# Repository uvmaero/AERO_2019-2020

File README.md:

# AERO_2019-2020

For all boards / designs specific to 2019 - 2020, CleanSpeed4.5

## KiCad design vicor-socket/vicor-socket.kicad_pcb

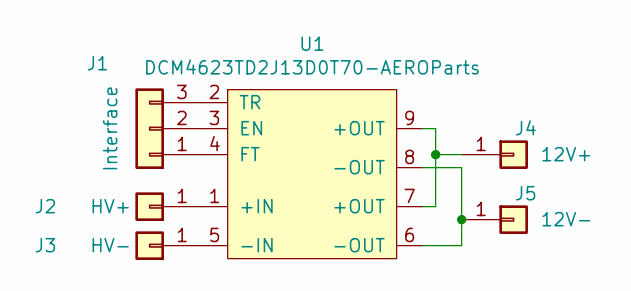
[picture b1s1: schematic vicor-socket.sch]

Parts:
J1: Interface; PinHeader_1x03_P2.54mm_Vertical
J2: HV+; MountingHole_3.2mm_M3_Pad_Via
J3: HV-; MountingHole_3.2mm_M3_Pad_Via
J4: 12V+; MountingHole_3.2mm_M3_Pad_Via
J5: 12V-; MountingHole_3.2mm_M3_Pad_Via
U1: DCM4623TD2J13D0T70-AEROParts; DCM4623TD2J13D0T70_w_landpattern

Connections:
unnamed: J1.1, U1.4 (FT)
unnamed: J1.2, U1.3 (EN)
unnamed: J1.3, U1.2 (TR)
unnamed: J2.1, U1.1 (+IN)
unnamed: J3.1, U1.5 (-IN)
unnamed: J4.1, U1.7 (+OUT), U1.9 (+OUT)
unnamed: J5.1, U1.6 (-OUT), U1.8 (-OUT)

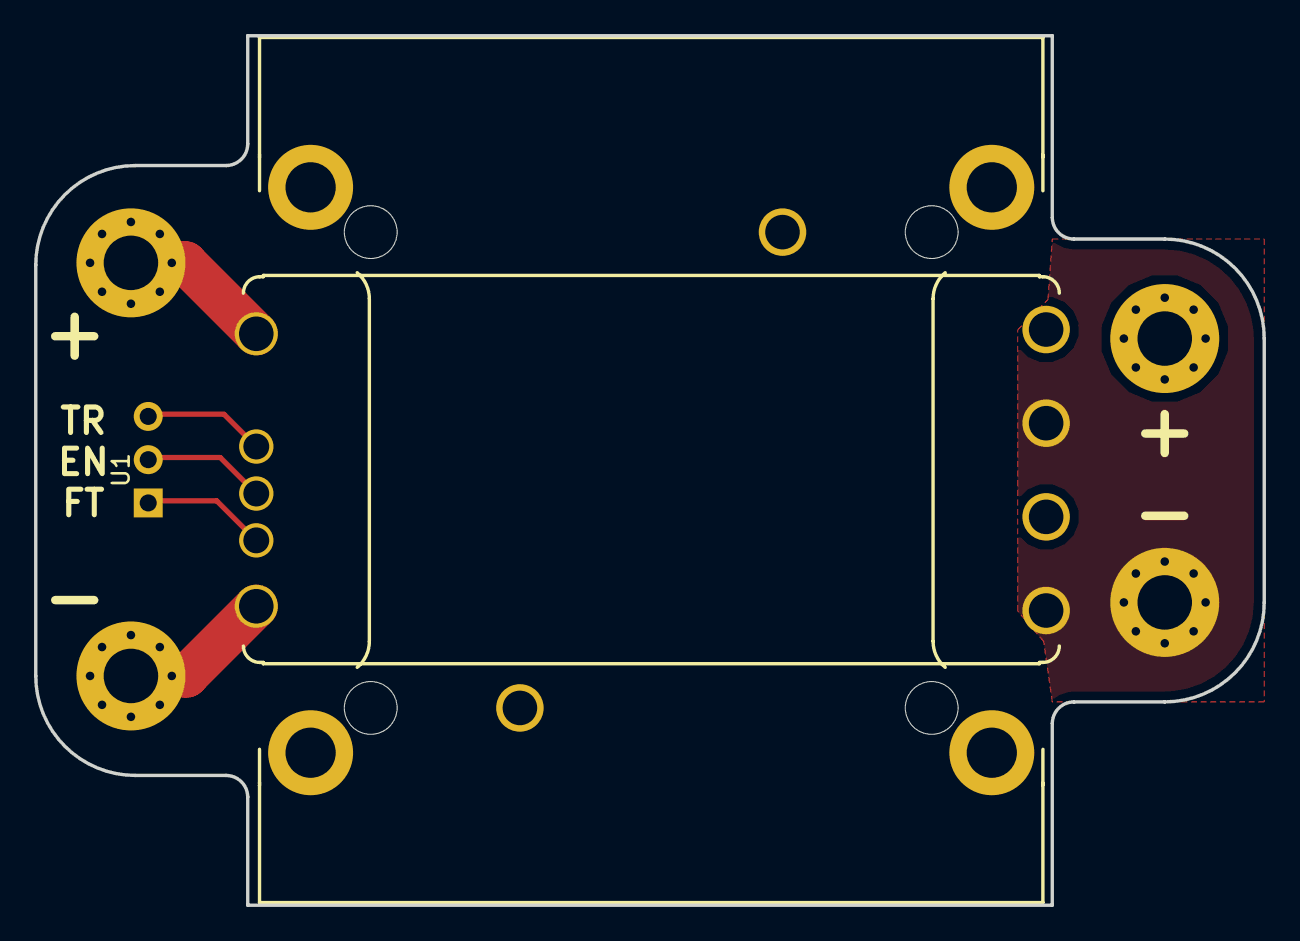
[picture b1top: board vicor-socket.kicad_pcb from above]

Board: 2 copper layers, 72.1 x 51.1 mm, 6 parts (1 on the bottom side), 7 nets.

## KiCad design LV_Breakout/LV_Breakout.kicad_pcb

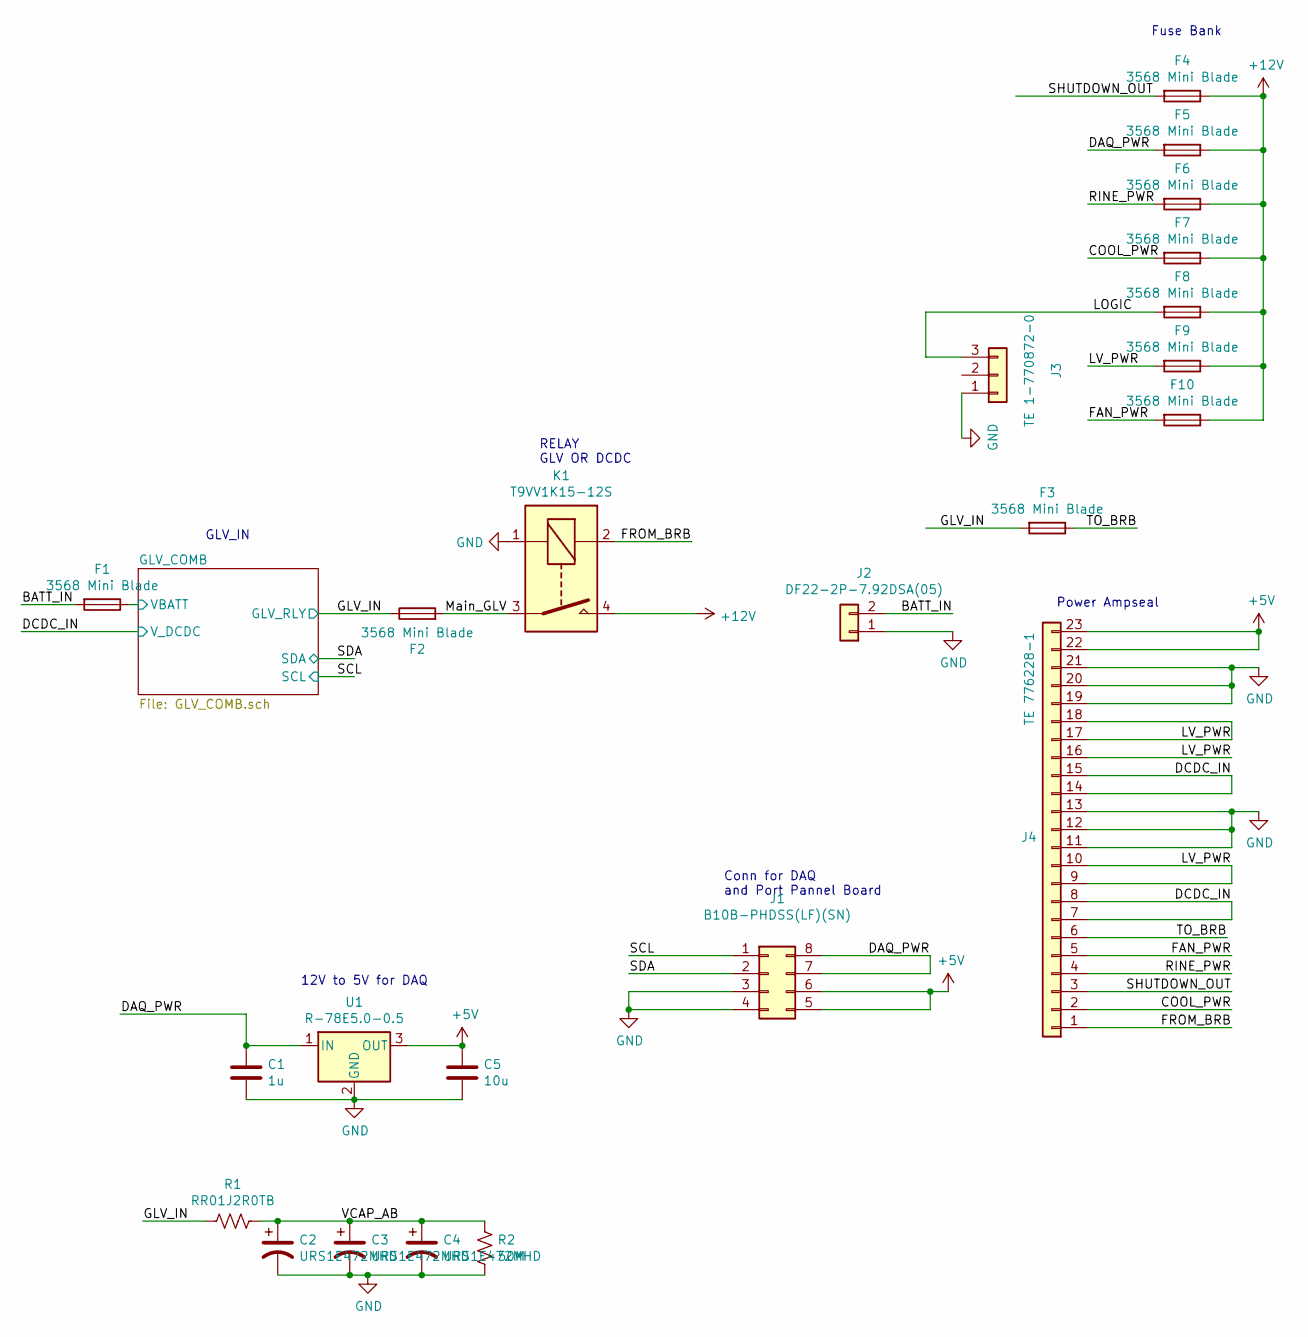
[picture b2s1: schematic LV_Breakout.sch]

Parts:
C1: 1u; C_0603_1608Metric_Pad1.05x0.95mm_HandSolder
C2, C3, C4: URS1E472MHD; CP_Radial_D18.0mm_P7.50mm
C5: 10u; C_0603_1608Metric_Pad1.05x0.95mm_HandSolder
F1, F2, F3, F4, F5, F6, F7, F8, F9, F10: 3568 Mini Blade; Fuseholder_Blade_Mini_Keystone_3568
J1: B10B-PHDSS(LF)(SN); JST_PHD_B8B-PHDSS_2x04_P2.00mm_Vertical
J2: DF22-2P-7.92DSA(05); DF22-2P-7.92DSA05
J3: TE 1-770872-0; TE_MATE-N-LOK_1-770870-x_1x03_P4.14mm_Vertical
J4: TE 776228-1; TE_1-776200-1_23pin_Vertical
K1: T9VV1K15-12S; RELAY_T9VV1K15-12S
R1: RR01J2R0TB; R_Axial_DIN0207_L6.3mm_D2.5mm_P10.16mm_Horizontal
R2: 50M; R_2512_6332Metric_Pad1.52x3.35mm_HandSolder
U1: R-78E5.0-0.5; Converter_DCDC_RECOM_R-78E-0.5_THT

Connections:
+5V: C5.1, J1.5, J1.6, J4.22, J4.23, U1.3 (OUT); also elsewhere on the board
+12V: F4.1, F5.1, F6.1, F7.1, F8.1, F9.1, F10.1, K1.4
/BATT_IN: F1.2, J2.2
/COOL_PWR: F7.2, J4.2
/DAQ_PWR: C1.1, F5.2, J1.7, J1.8, U1.1 (IN)
/DCDC_IN: J4.7, J4.8, J4.14, J4.15; also elsewhere on the board
/FAN_PWR: F10.2, J4.5
/FROM_BRB: J4.1, K1.2
/GLV_COMB/VBATT: F1.1; also elsewhere on the board
/GLV_IN: F2.1, F3.2, R1.2; also elsewhere on the board
/LOGIC: F8.2, J3.3
/LV_PWR: F9.2, J4.9, J4.10, J4.16, J4.17, J4.18
/Main_GLV: F2.2, K1.3
/RINE_PWR: F6.2, J4.4
/SCL: J1.1; also elsewhere on the board
/SDA: J1.2; also elsewhere on the board
/SHUTDOWN_OUT: F4.2, J4.3
/TO_BRB: F3.1, J4.6
/VCAP_AB: C2.1, C3.1, C4.1, R1.1, R2.1
GND: C1.2, C2.2, C3.2, C4.2, C5.2, J1.3, J1.4, J2.1, J3.1, J4.11, J4.12, J4.13, J4.19, J4.20, J4.21, K1.1, R2.2, U1.2 (GND); also elsewhere on the board

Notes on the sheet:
GLV_IN
Power Ampseal
RELAY GLV OR DCDC
Fuse Bank
12V to 5V for DAQ
Conn for DAQ and Port Pannel Board

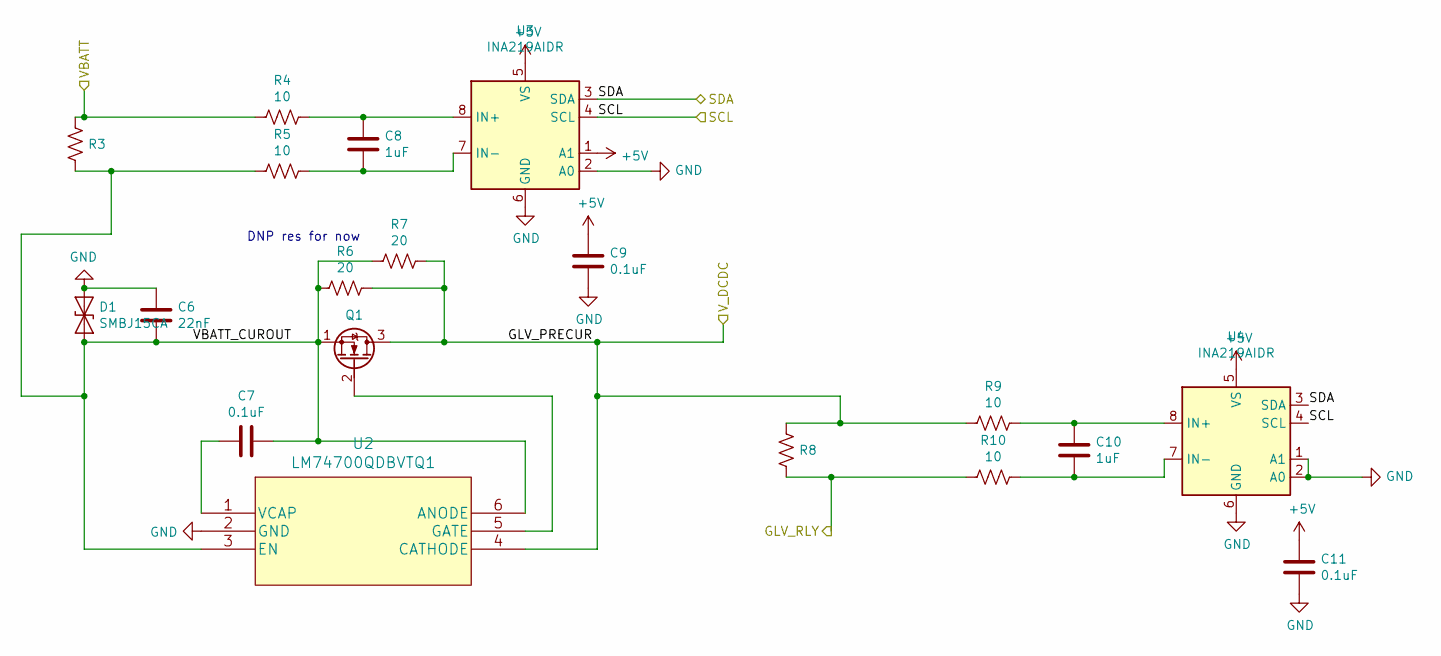
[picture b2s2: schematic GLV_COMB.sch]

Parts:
C6: 22nF; C_0603_1608Metric_Pad1.05x0.95mm_HandSolder
C7, C9, C11: 0.1uF; C_0603_1608Metric_Pad1.05x0.95mm_HandSolder
C8, C10: 1uF; C_0603_1608Metric_Pad1.05x0.95mm_HandSolder
D1: SMBJ15CA; DO-214AA
Q1: CSD18563Q5A; VSONP-8-1EP_5x6_P1.27mm
R3, R8: KRL6432E-M-R003-F-T1
R4, R5, R9, R10: 10; R_0805_2012Metric_Pad1.15x1.40mm_HandSolder
R6, R7: 20; R_2512_6332Metric_Pad1.52x3.35mm_HandSolder
U2: LM74700QDBVTQ1; SOT-23-6_Handsoldering
U3, U4: INA219AIDR; SOIC-8_3.9x4.9mm_P1.27mm

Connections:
+5V: C9.1, C11.1, U3.1 (A1), U3.5 (VS), U4.5 (VS); also elsewhere on the board
/DCDC_IN: Q1.3 (D), R6.1, R7.1, R8.1, R9.2, U2.4 (CATHODE); also elsewhere on the board
/GLV_COMB/VBATT: R3.1, R4.2; also elsewhere on the board
/GLV_COMB/VBATT_CUROUT: C6.2, C7.2, D1.1 (A1), Q1.1 (S), R3.2, R5.2, R6.2, R7.2, U2.3 (EN), U2.6 (ANODE)
/GLV_IN: R8.2, R10.2; also elsewhere on the board
/SCL: U3.4 (SCL), U4.4 (SCL); also elsewhere on the board
/SDA: U3.3 (SDA), U4.3 (SDA); also elsewhere on the board
GND: C6.1, C9.2, C11.2, D1.2 (A2), U2.2 (GND), U3.2 (A0), U3.6 (GND), U4.1 (A1), U4.2 (A0), U4.6 (GND); also elsewhere on the board
unnamed: C7.1, U2.1 (VCAP)
unnamed: C8.1, R4.1, U3.8 (IN+)
unnamed: C8.2, R5.1, U3.7 (IN-)
unnamed: C10.1, R9.1, U4.8 (IN+)
unnamed: C10.2, R10.1, U4.7 (IN-)
unnamed: Q1.2 (G), U2.5 (GATE)

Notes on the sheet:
DNP res for now

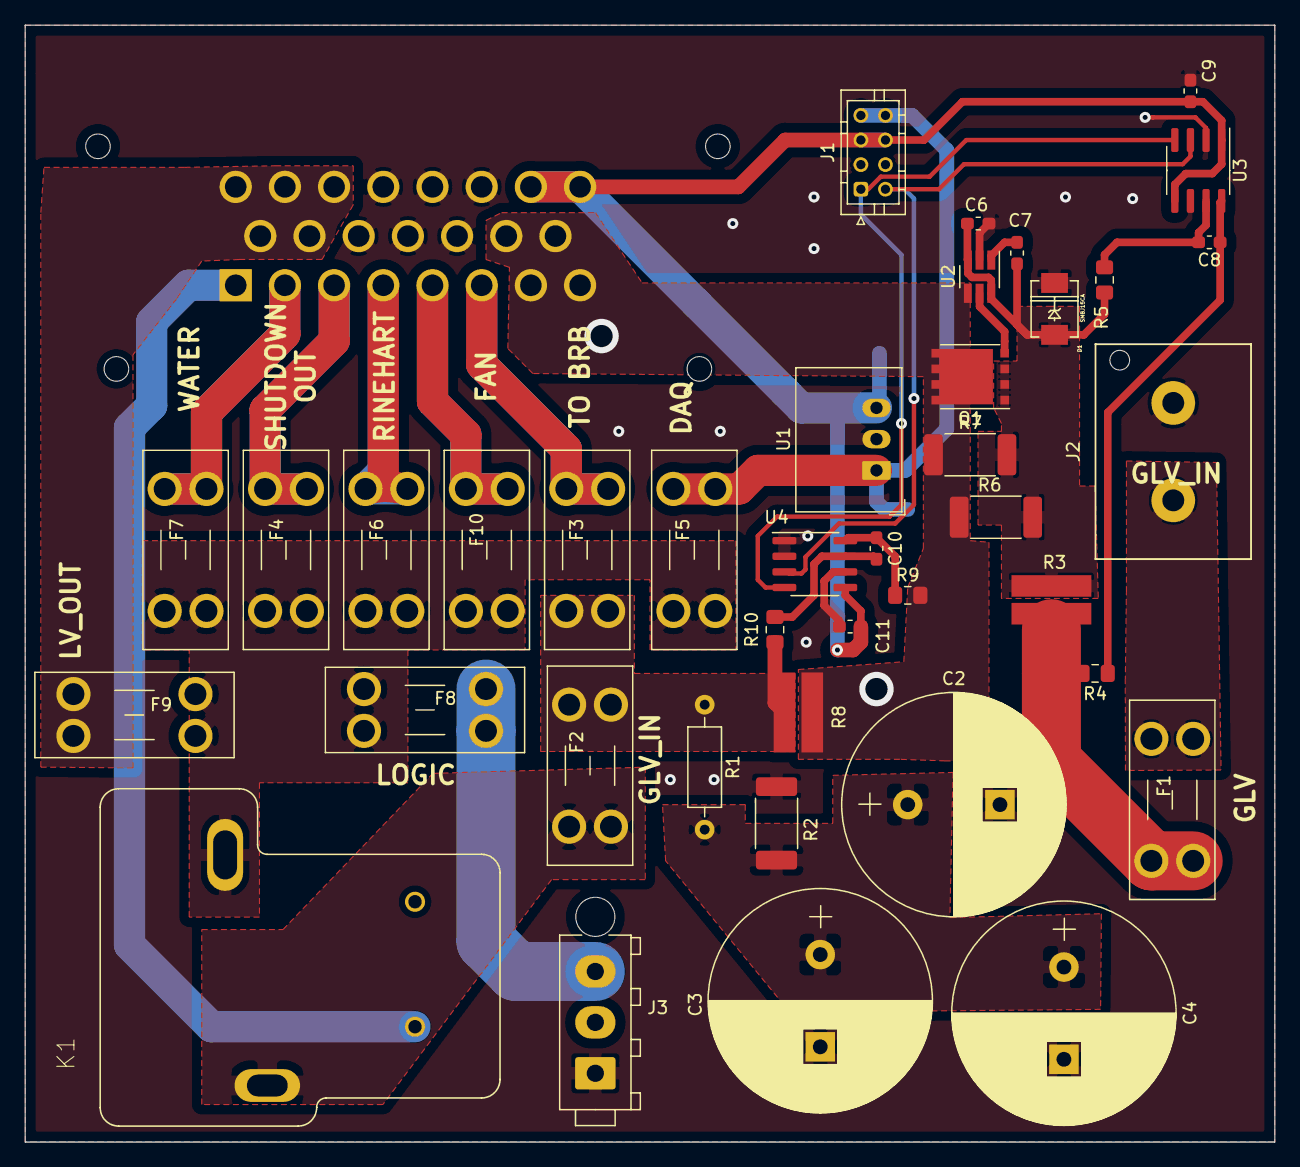
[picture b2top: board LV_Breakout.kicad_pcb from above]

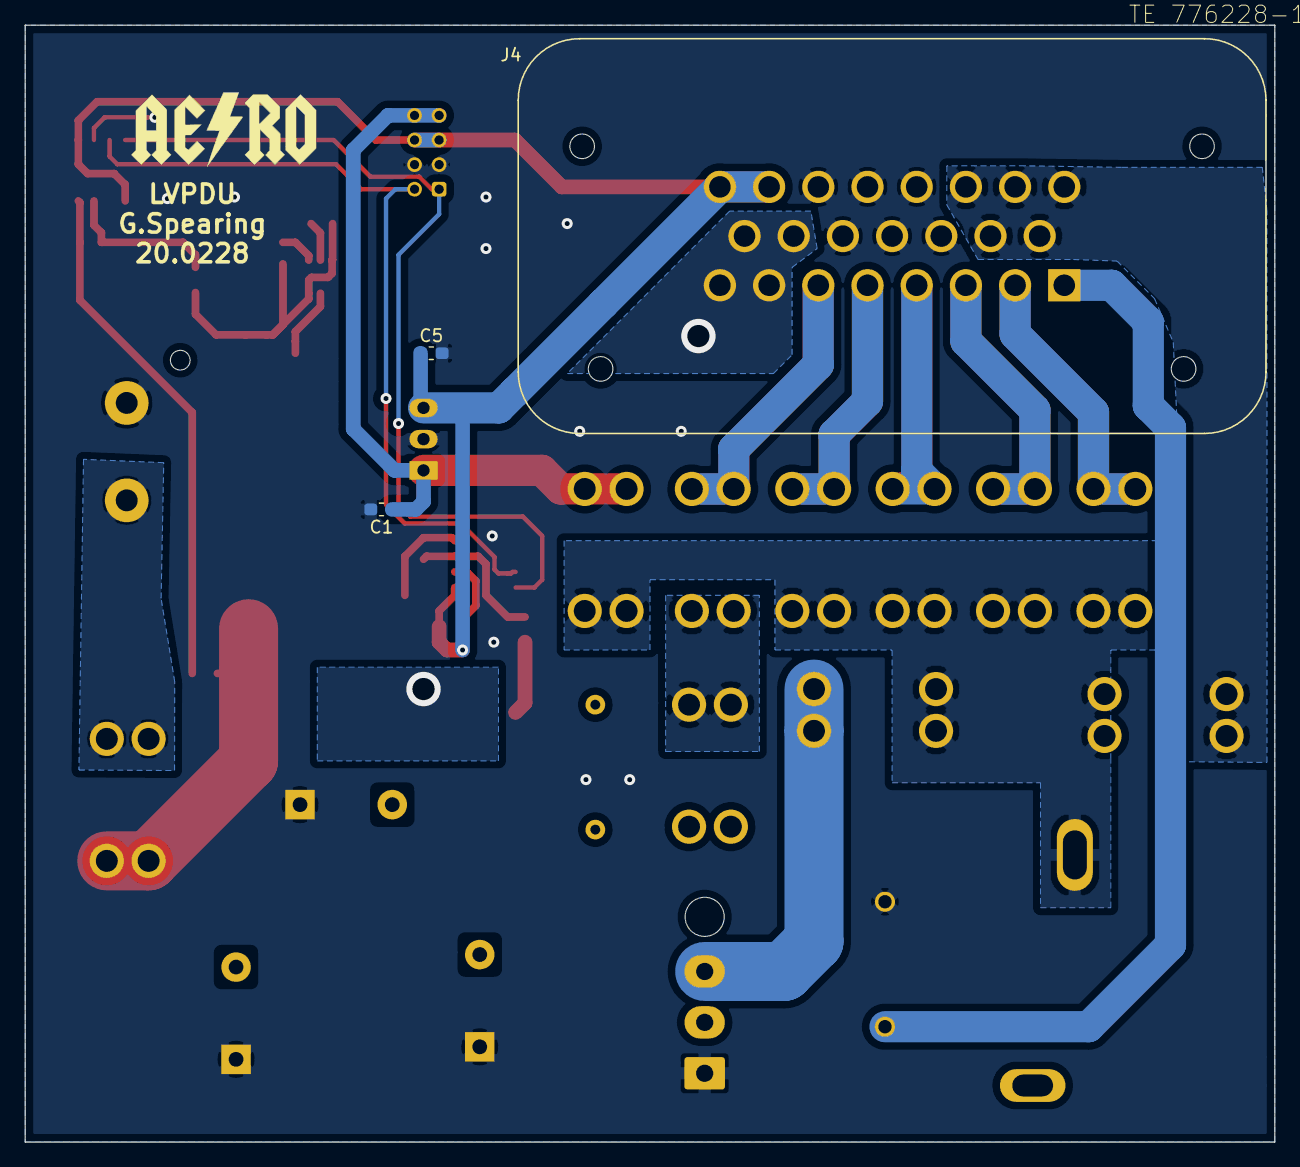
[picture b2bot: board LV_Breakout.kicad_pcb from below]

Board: 2 copper layers, 101.6 x 90.8 mm, 42 parts (3 on the bottom side), 27 nets.

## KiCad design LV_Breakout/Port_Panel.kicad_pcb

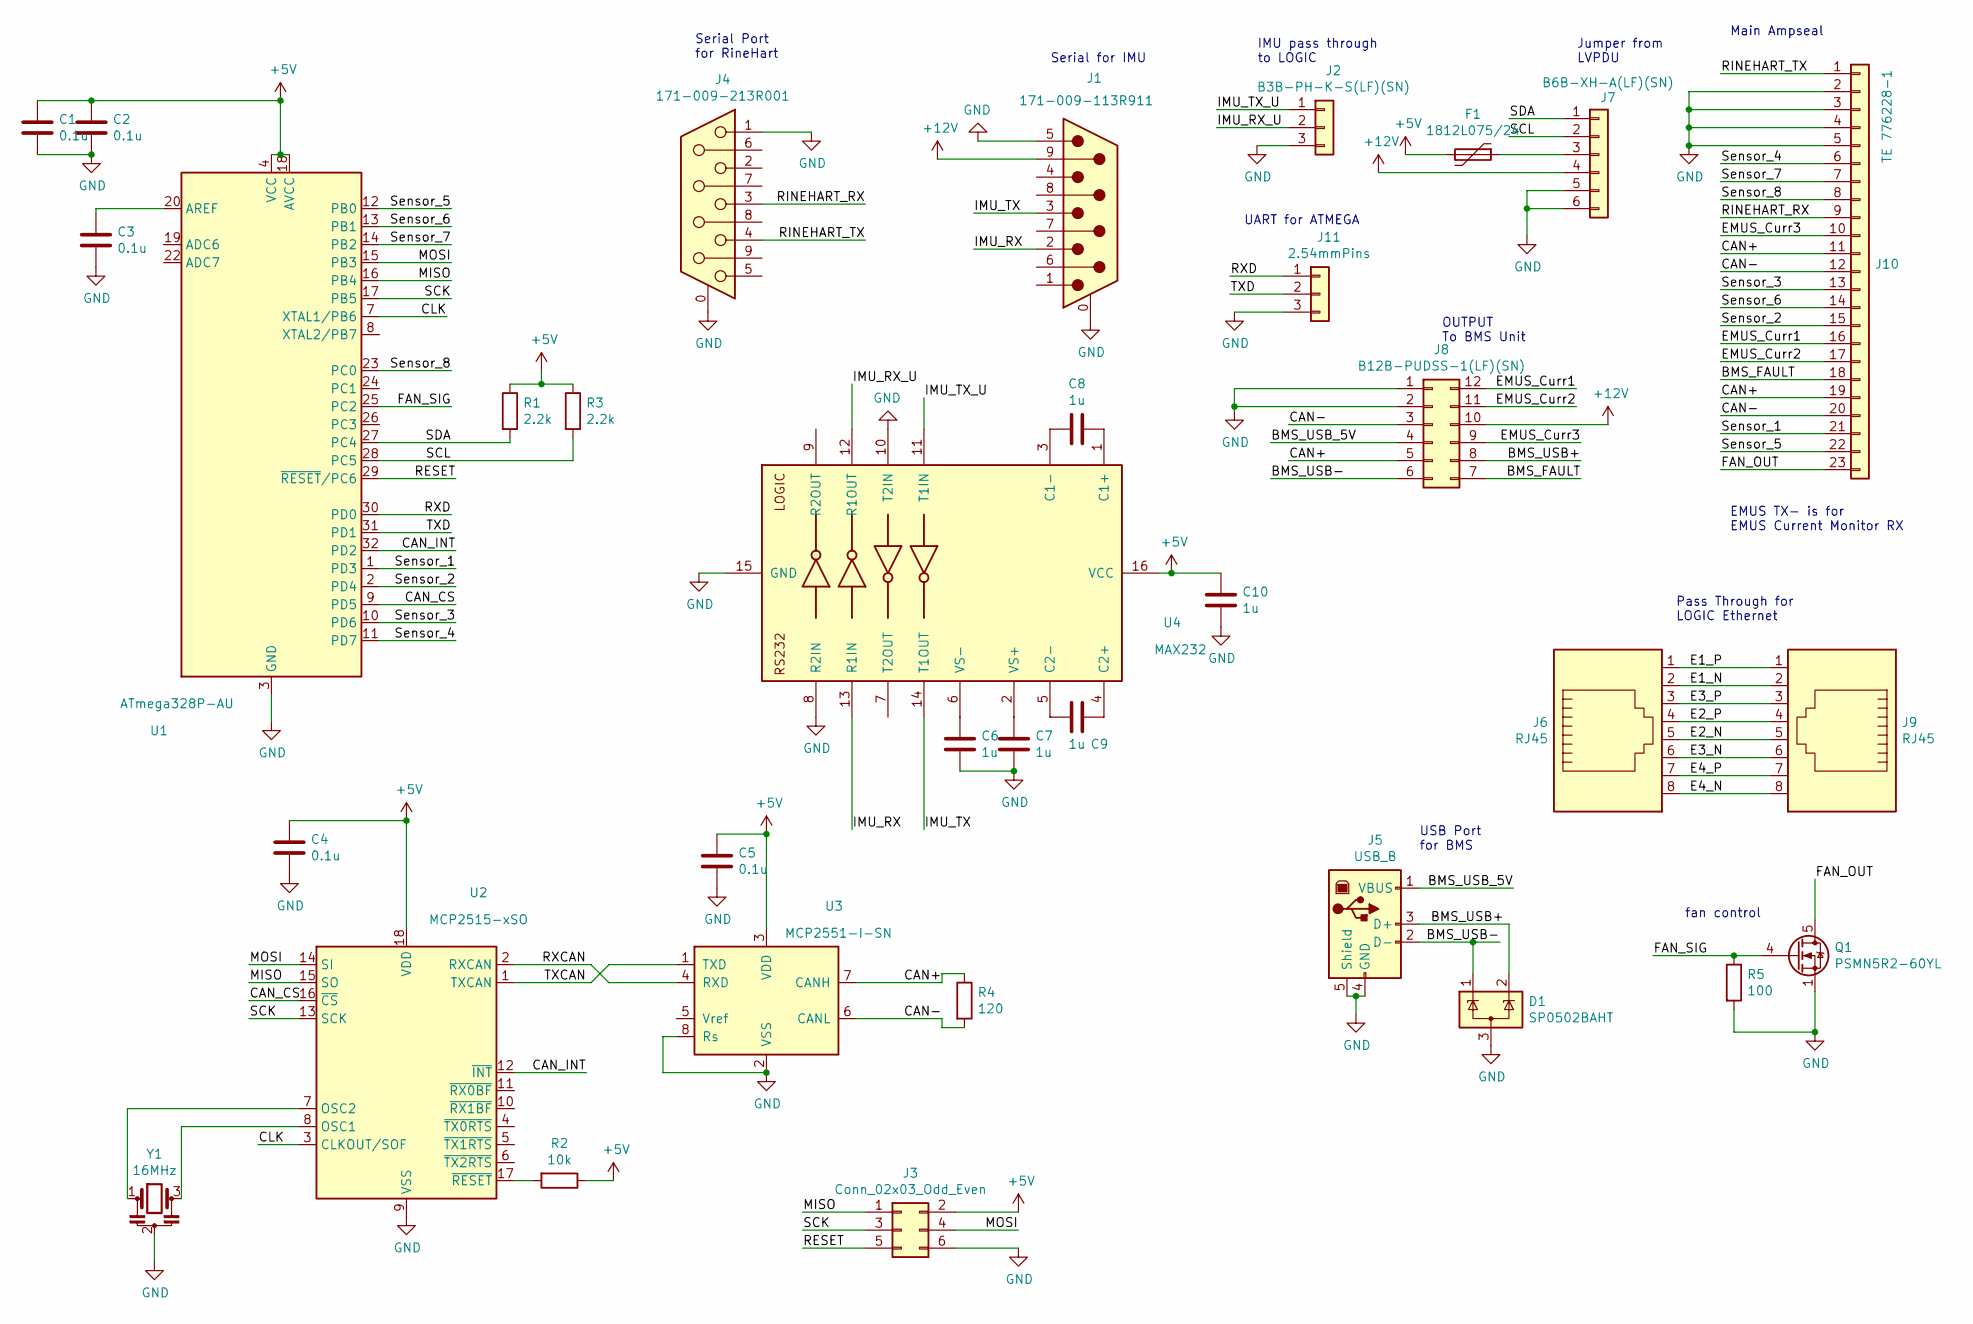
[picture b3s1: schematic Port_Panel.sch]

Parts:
C1, C2, C3, C4, C5: 0.1u; C_0603_1608Metric_Pad1.05x0.95mm_HandSolder
C6, C7, C8, C9, C10: 1u; C_0603_1608Metric_Pad1.05x0.95mm_HandSolder
D1: SP0502BAHT; SOT-23
F1: 1812L075/24; Fuse_1812_4532Metric_Pad1.30x3.40mm_HandSolder
J1: 171-009-113R911; DSUB-9_Male_Vertical_P2.77x2.84mm_MountingHoles
J2: B3B-PH-K-S(LF)(SN); JST_PH_B3B-PH-K_1x03_P2.00mm_Vertical
J3: Conn_02x03_Odd_Even; PinHeader_2x03_P2.54mm_Vertical
J4: 171-009-213R001; DSUB-9_Female_Vertical_P2.77x2.84mm_MountingHoles
J5: USB_B; USB_B_TE_5787834_Vertical
J6: RJ45; RJ45_OST_PJ012-8P8CX_Vertical
J7: B6B-XH-A(LF)(SN); JST_PH_B6B-PH-K_1x06_P2.00mm_Vertical
J8: B12B-PUDSS-1(LF)(SN); JST_PHD_B12B-PHDSS_2x06_P2.00mm_Vertical
J9: RJ45; RJ45_Amphenol_54602-x08_Horizontal
J10: TE 776228-1; TE_1-776200-1_23pin_Vertical
J11: 2.54mmPins; PinHeader_1x03_P2.54mm_Vertical
Q1: PSMN5R2-60YL; LFPAK56
R1, R3: 2.2k; R_0603_1608Metric_Pad1.05x0.95mm_HandSolder
R2: 10k; R_0603_1608Metric_Pad1.05x0.95mm_HandSolder
R4: 120; R_0603_1608Metric_Pad1.05x0.95mm_HandSolder
R5: 100; R_0603_1608Metric_Pad1.05x0.95mm_HandSolder
U1: ATmega328P-AU; TQFP-32_7x7mm_P0.8mm
U2: MCP2515-xSO; SOIC-18W_7.5x11.6mm_P1.27mm
U3: MCP2551-I-SN; SOIC-8_3.9x4.9mm_P1.27mm
U4: MAX232; SOIC-16_3.9x9.9mm_P1.27mm
Y1: 16MHz; Resonator_SMD_muRata_CSTxExxV-3Pin_3.0x1.1mm_HandSoldering

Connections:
+5V: C1.1, C2.1, C4.1, C5.1, C10.1, F1.2, J3.2, R1.1, R2.1, R3.1, U1.4 (VCC), U1.6 (VCC), U1.18 (AVCC), U2.18 (VDD), U3.3 (VDD), U4.16 (VCC)
+12V: J1.6, J1.9, J7.4, J8.10
/BMS_FAULT: J8.7, J10.18
/BMS_USB+: D1.2 (K), J5.3 (D+), J8.8
/BMS_USB-: D1.1 (K), J5.2 (D-), J8.6
/BMS_USB_5V: J5.1 (VBUS), J8.4
/CAN+: J8.5, J10.11, J10.19, R4.1, U3.7 (CANH)
/CAN-: J8.3, J10.12, J10.20, R4.2, U3.6 (CANL)
/CAN_CS: U1.9 (PD5), U2.16 (~CS)
/CAN_INT: U1.32 (PD2), U2.12 (~INT)
/CLK: U1.7 (XTAL1/PB6), U2.3 (CLKOUT/SOF)
/E1_N: J6.2, J9.2
/E1_P: J6.1, J9.1
/E2_N: J6.5, J9.5
/E2_P: J6.4, J9.4
/E3_N: J6.6, J9.6
/E3_P: J6.3, J9.3
/E4_N: J6.8, J9.8
/E4_P: J6.7, J9.7
/EMUS_Curr1: J8.12, J10.16
/EMUS_Curr2: J8.11, J10.17
/EMUS_Curr3: J8.9, J10.10
/FAN_OUT: J10.23, Q1.5 (D)
/FAN_SIG: Q1.4 (G), R5.1, U1.25 (PC2)
/IMU_RX: J1.2, U4.13 (R1IN)
/IMU_RX_U: J2.2, U4.12 (R1OUT)
/IMU_TX: J1.3, U4.14 (T1OUT)
/IMU_TX_U: J2.1, U4.11 (T1IN)
/MISO: J3.1, U1.16 (PB4), U2.15 (SO)
/MOSI: J3.4, U1.15 (PB3), U2.14 (SI)
/RESET: J3.5, U1.29 (~RESET~/PC6)
/RINEHART_RX: J4.3, J10.9
/RINEHART_TX: J4.4, J10.1
/RXCAN: U2.2 (RXCAN), U3.4 (RXD)
/RXD: J11.1, U1.30 (PD0)
/SCK: J3.3, U1.17 (PB5), U2.13 (SCK)
/SCL: J7.2, R3.2, U1.28 (PC5)
/SDA: J7.1, R1.2, U1.27 (PC4)
/Sensor_1: J10.21, U1.1 (PD3)
/Sensor_2: J10.15, U1.2 (PD4)
/Sensor_3: J10.13, U1.10 (PD6)
/Sensor_4: J10.6, U1.11 (PD7)
/Sensor_5: J10.22, U1.12 (PB0)
/Sensor_6: J10.14, U1.13 (PB1)
/Sensor_7: J10.7, U1.14 (PB2)
/TXCAN: U2.1 (TXCAN), U3.1 (TXD)
/TXD: J11.2, U1.31 (PD1)
GND: C1.2, C2.2, C3.2, C4.2, C5.2, C6.2, C7.2, C10.2, D1.3 (A), J1.0 (PAD), J1.5, J2.3, J3.6, J4.0 (PAD), J4.1, J5.4 (GND), J5.5 (Shield), J7.5, J7.6, J8.1, J8.2, J10.2, J10.3, J10.4, J10.5, J11.3, Q1.1 (S), Q1.2 (S), Q1.3 (S), R5.2, U1.3 (GND), U1.5 (GND), U1.21 (GND), U2.9 (VSS), U3.2 (VSS), U3.8 (Rs), U4.8 (R2IN), U4.10 (T2IN), U4.15 (GND), Y1.2; also elsewhere on the board
unnamed: C3.1, U1.20 (AREF)
unnamed: C6.1, U4.6 (VS-)
unnamed: C7.1, U4.2 (VS+)
unnamed: C8.1, U4.1 (C1+)
unnamed: C8.2, U4.3 (C1-)
unnamed: C9.1, U4.4 (C2+)
unnamed: C9.2, U4.5 (C2-)
unnamed: F1.1, J7.3
unnamed: R2.2, U2.17 (~RESET)
unnamed: U2.7 (OSC2), Y1.1
unnamed: U2.8 (OSC1), Y1.3

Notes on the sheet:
Pass Through for LOGIC Ethernet
Jumper from LVPDU
OUTPUT To BMS Unit
USB Port for BMS
Serial Port for RineHart
Main Ampseal
EMUS TX- is for EMUS Current Monitor RX
Serial for IMU
IMU pass through to LOGIC
fan control
UART for ATMEGA

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
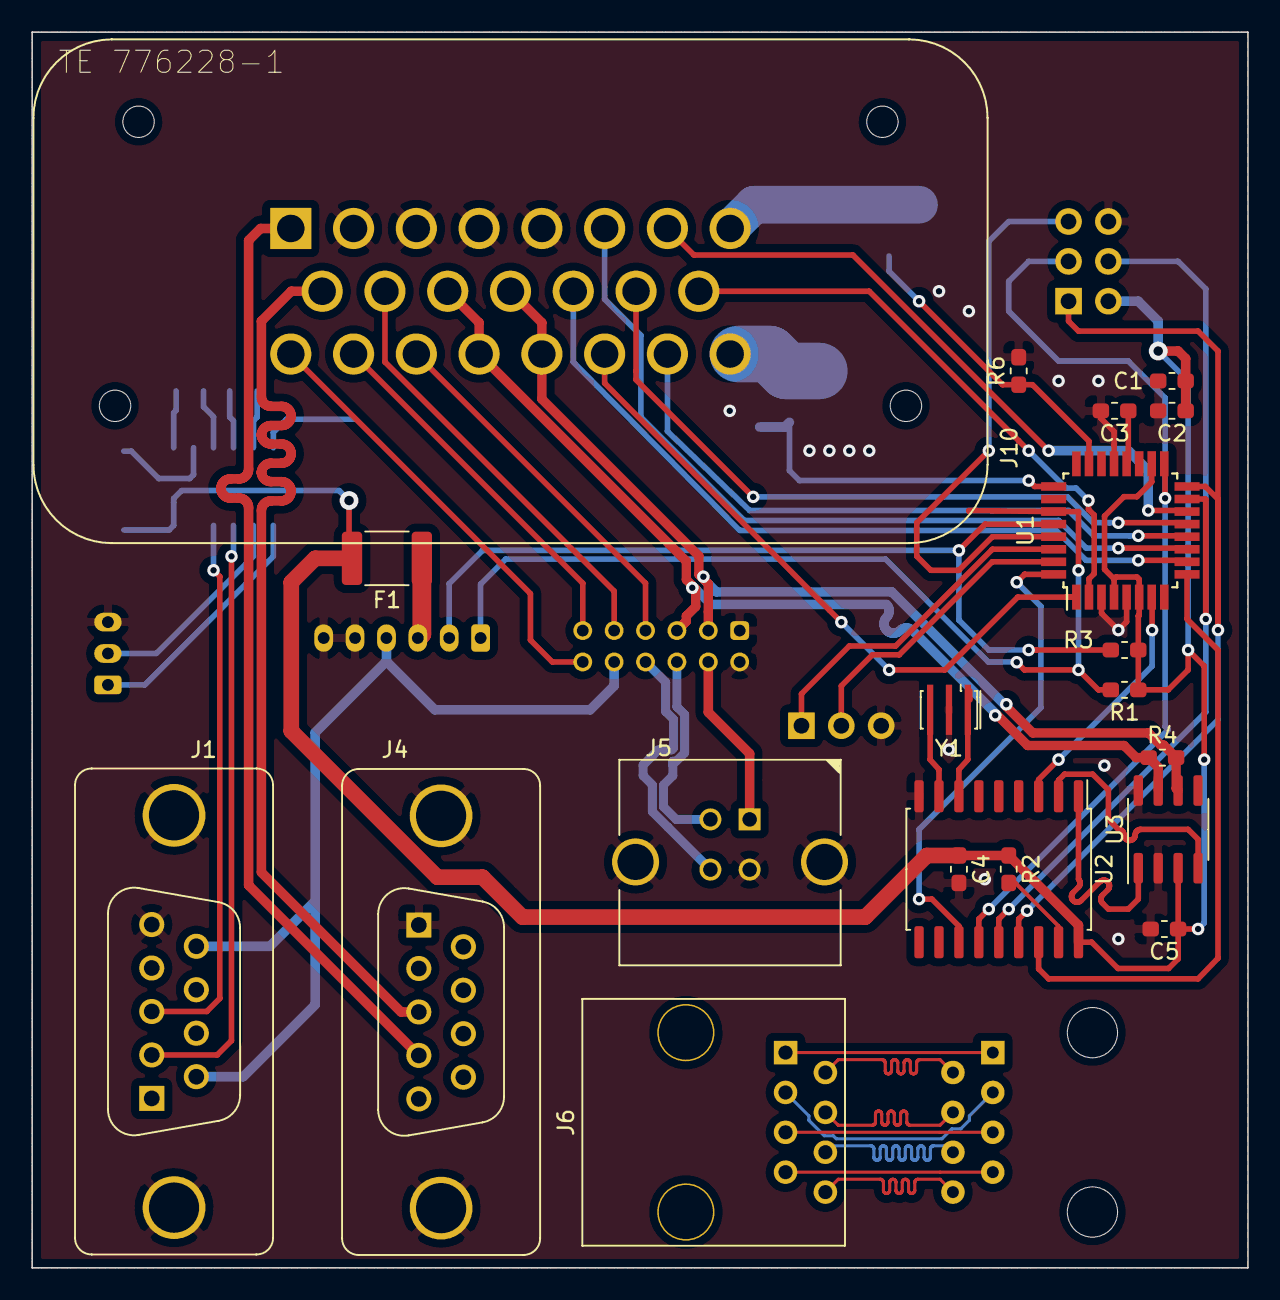
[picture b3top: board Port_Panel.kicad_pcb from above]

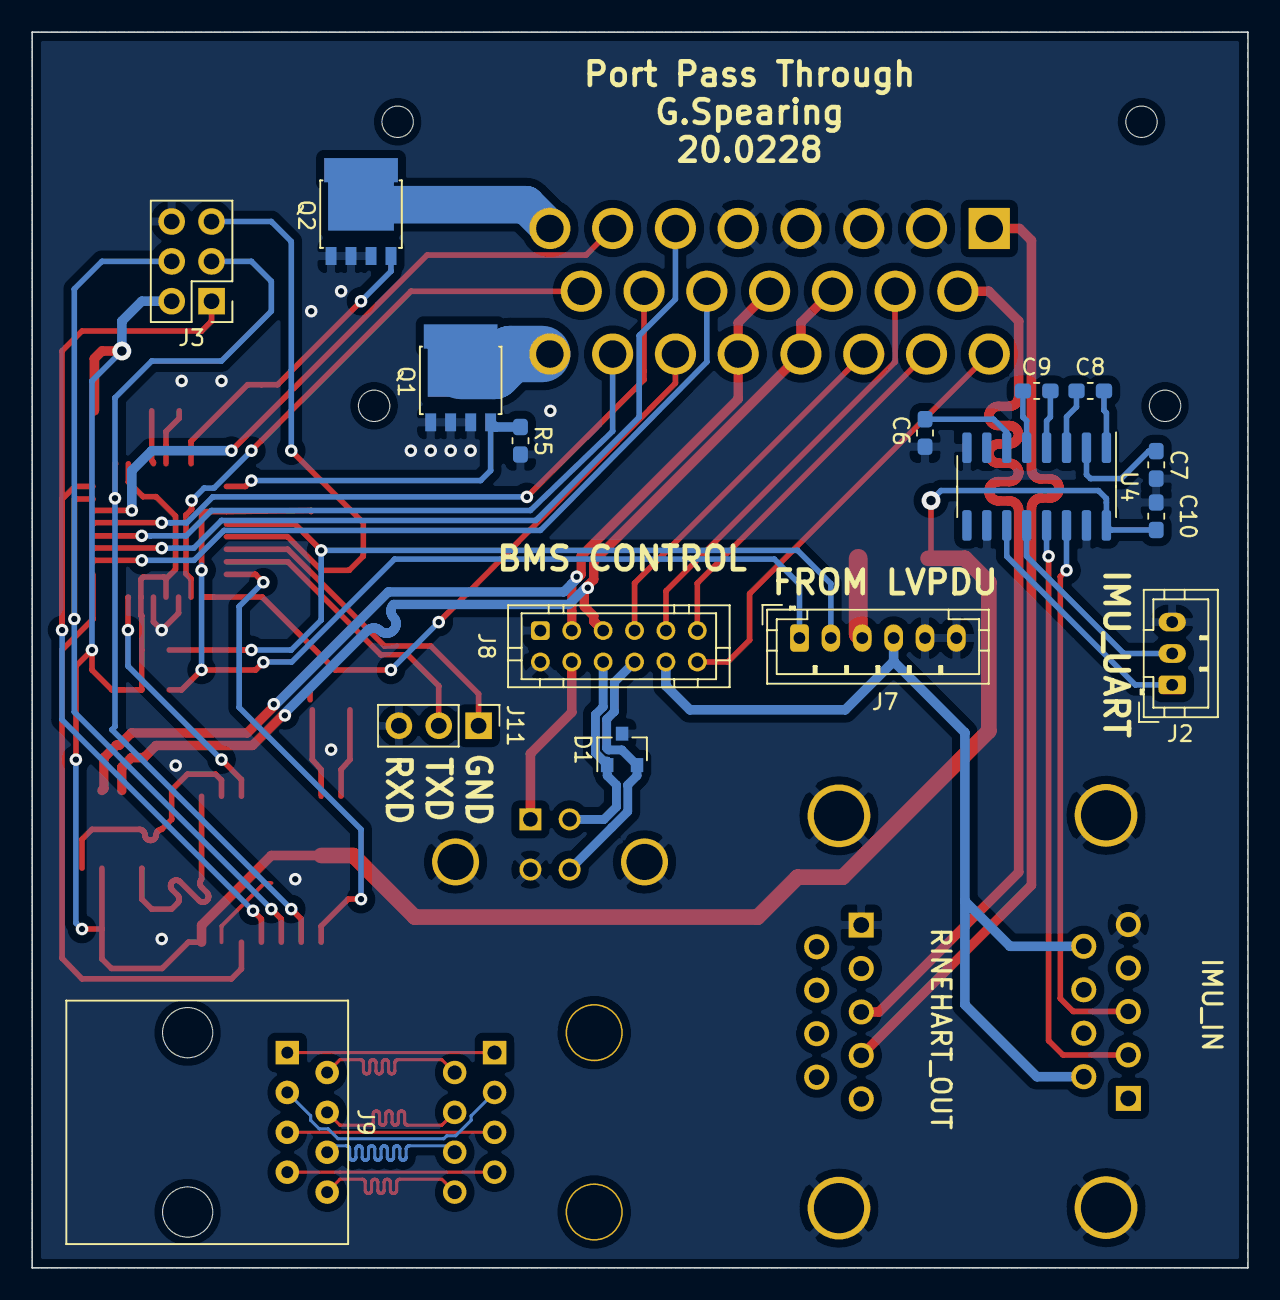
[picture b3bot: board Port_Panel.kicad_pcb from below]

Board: 2 copper layers, 77.5 x 78.7 mm, 36 parts (16 on the bottom side), 61 nets.

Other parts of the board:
Q2: PSMN5R2-60YL; LFPAK56
R6: 100; R_0603_1608Metric_Pad1.05x0.95mm_HandSolder

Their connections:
GND: Q2.1, Q2.2, Q2.3, R6.2; also elsewhere on the board

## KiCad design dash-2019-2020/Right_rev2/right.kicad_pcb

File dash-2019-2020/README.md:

# dash-2019-2020
Dashboard PCB for 2019-2020

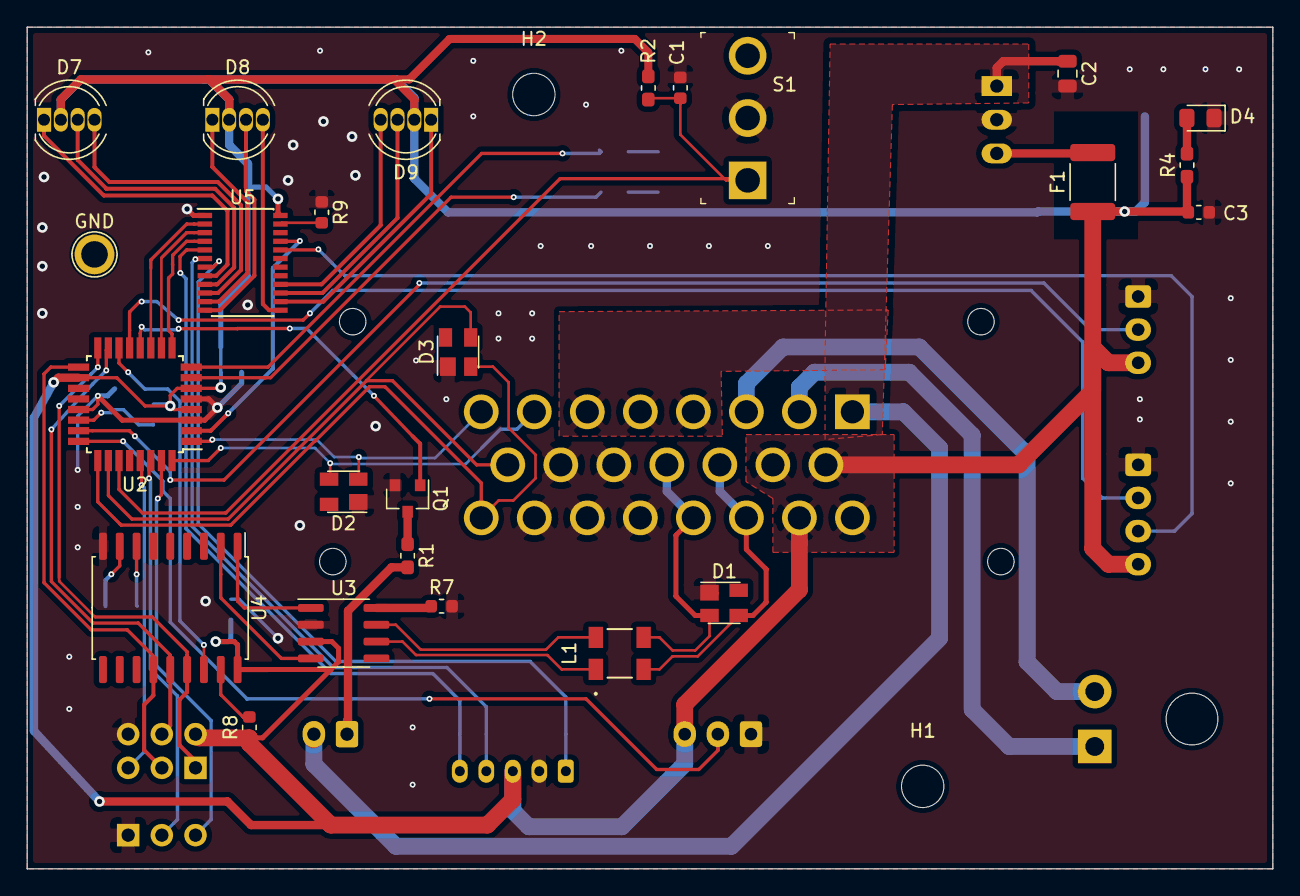
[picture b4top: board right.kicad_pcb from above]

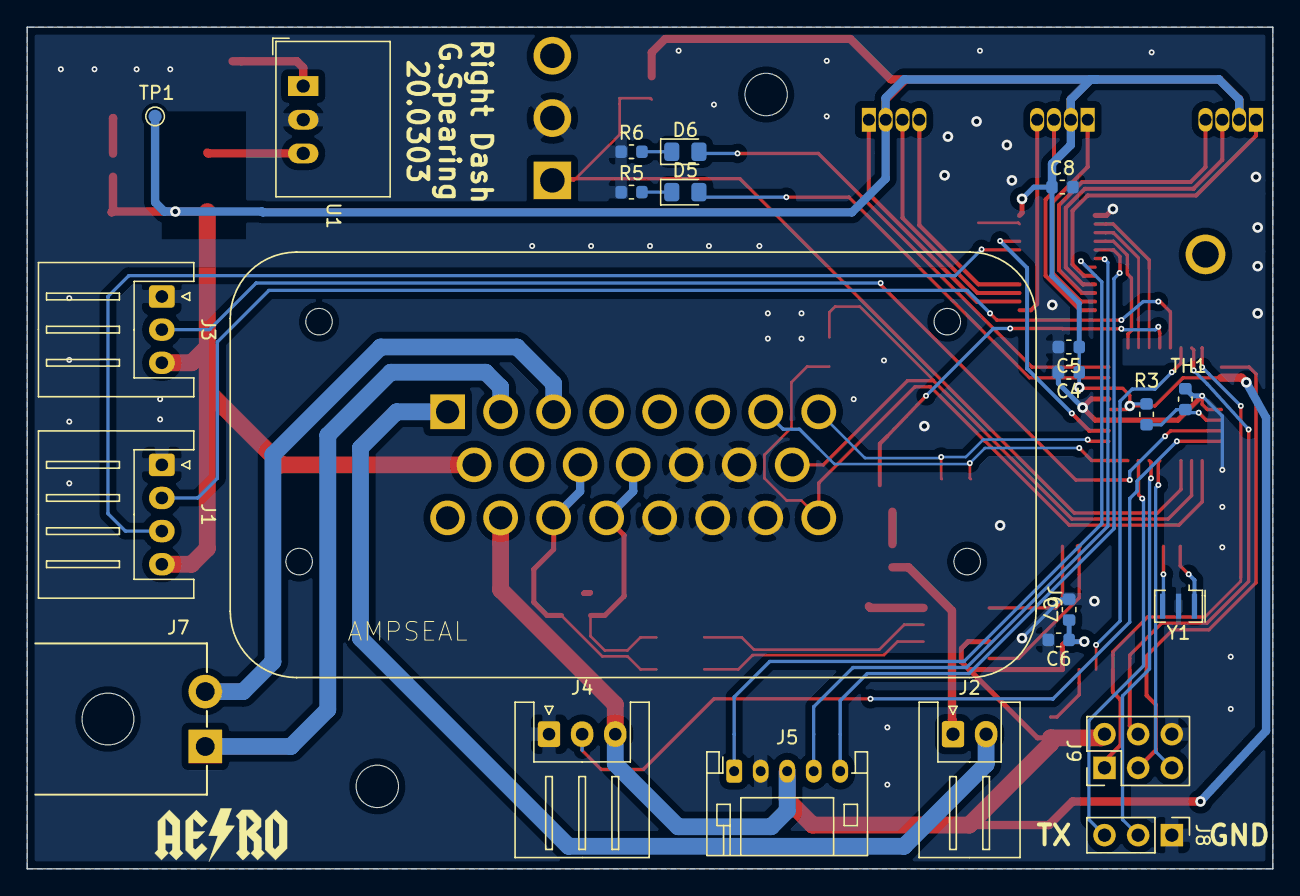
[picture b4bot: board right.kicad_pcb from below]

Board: 2 copper layers, 94.0 x 63.5 mm, 50 parts (23 on the bottom side), 58 nets.

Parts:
C1, C6, C7: 0.1uF; C_0603_1608Metric
C2: 10u; C_0805_2012Metric
C3: 10u; C_0603_1608Metric
C4, C5, C8: 0.1u; C_0603_1608Metric
D1, D2, D3: SP0503BAHT; SOT-143
D4: SM0805YCL; LED_0805_2012Metric_Pad1.15x1.40mm_HandSolder
D5: SM0805GCL; LED_0805_2012Metric_Pad1.15x1.40mm_HandSolder
D6: SM0805HCL; LED_0805_2012Metric_Pad1.15x1.40mm_HandSolder
D7: COOLING_IND_1; LED_D5.0mm-4_RGB
D8: COOLING_IND_2; LED_D5.0mm-4_RGB
D9: COOLING_IND_3; LED_D5.0mm-4_RGB
F1: MF-MSMF050; Fuse_1812_4532Metric_Pad1.30x3.40mm_HandSolder
GND: TestPoint_Plated_Hole_D2.0mm
H1, H2: MountingHole; MountingHole_3.2mm_M3
J1: JST-XH; JST_XH_S4B-XH-A_1x04_P2.50mm_Horizontal
J2: JST-XH; JST_XH_S2B-XH-A_1x02_P2.50mm_Horizontal
J3, J4: JST-XH; JST_XH_S3B-XH-A_1x03_P2.50mm_Horizontal
J5: B5B-PH-SM4-TB(LF)(SN); JST_PH_S5B-PH-K_1x05_P2.00mm_Horizontal
J6: AMPSEAL; TE_1-776228-1_23P_VERT
J7: 1-770966-0
J8: Header 1x3 0.1in; PinHeader_1x03_P2.54mm_Vertical
J9: Header 2x3 0.1in; PinHeader_2x03_P2.54mm_Vertical
L1: SRF4532; SRF4532-220Y
Q1: MMBT2222ALT1G; SOT-23
R1: 1k; R_0603_1608Metric_Pad1.05x0.95mm_HandSolder
R2: 10k; R_0603_1608Metric_Pad1.05x0.95mm_HandSolder
R3: RES 0603 10k 1%; R_0603_1608Metric
R4: 1.5k; R_0603_1608Metric_Pad1.05x0.95mm_HandSolder
R5, R6: 1.5k; R_0603_1608Metric
R7, R8: 10k; R_0603_1608Metric
R9: 1k; R_0603_1608Metric
S1: 100SP1T1B4M2QE; Toggle_Switch_100SP1T1B4M2QE
TH1: NCU18XH103F60RB; R_0603_1608Metric
TP1: TestPoint; TestPoint_Pad_D1.0mm
U1: R-78E5.0-1; Converter_DCDC_RECOM_R-78E-0.5_THT
U2: ATmega328P-AU; TQFP-32_7x7mm_P0.8mm
U3: MCP2551-I-SN; SOIC-8_3.9x4.9mm_P1.27mm
U4: MCP2515-xSO; SOIC-18W_7.5x11.6mm_P1.27mm
U5: STP16CP05; TSSOP-24_4.4x7.8mm_P0.65mm
Y1: Resonator; Resonator_SMD_muRata_CSTxExxV-3Pin_3.0x1.1mm

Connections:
+5V: C3.1, C4.1, C5.1, C6.1, C7.1, C8.1, D7.2, D8.2, D9.2, F1.1, J1.4, J3.3, J4.3, J5.3, J6.9, J6.10, J6.16, J6.17, J9.2, R2.1, R3.1, R4.1, R8.1, TP1.1, U2.4, U2.6, U2.18, U3.3, U4.18, U5.24
+12V: C2.1, J2.2, J6.1, J6.4, J6.5, J6.6, U1.1
/BRAKE: J4.2, U2.24
/CAN+: D1.2, J6.12, J6.19, L1.2
/CAN-: D1.3, J6.11, J6.18, L1.4
/COAST: J3.2, U2.23
/COOLING_MODE: C1.1, R2.2, S1.1, U2.27
/DAMPER_L: D3.3, J6.15, U2.26
/DAMPER_R: D3.2, J6.23, U2.25
/LED1: D5.2, U2.7
/LED2: D6.2, U2.8
/LED_CLK: U2.10, U5.3
/LED_SDI: U2.11, U5.2
/LEDs/~COOLING_IND1B: D7.4, U5.10
/LEDs/~COOLING_IND1G: D7.3, U5.9
/LEDs/~COOLING_IND1R: D7.1, U5.8
/LEDs/~COOLING_IND2B: D8.4, U5.13
/LEDs/~COOLING_IND2G: D8.3, U5.12
/LEDs/~COOLING_IND2R: D8.1, U5.11
/LEDs/~COOLING_IND3B: D9.4, U5.16
/LEDs/~COOLING_IND3G: D9.3, U5.15
/LEDs/~COOLING_IND3R: D9.1, U5.14
/MISO: J9.1, U2.16, U4.15
/MOSI: J9.4, U2.15, U4.14
/NTC1: R3.2, TH1.1, U2.22
/RESET: J9.5, U2.29
/RTD_BTN: J1.2, U2.13
/RTD_IND: Q1.1, U2.12
/SCK: J9.3, U2.17, U4.13
/SHUTDOWN_IN: J6.2, J7.1
/SHUTDOWN_OUT: J6.3, J7.2
/SPEED_L: D2.2, J6.8, U2.1
/SPEED_R: D2.3, J6.7, U2.32
/UART_RXD: J8.2, U2.30
/UART_TXD: J8.3, U2.31
/~CAN_CS: U2.14, U4.16
/~LED_LE: U2.9, U5.4
/~LED_OE: U2.2, U5.21
GND: C1.2, C2.2, C3.2, C4.2, C5.2, C6.2, C7.2, C8.2, D1.1, D2.1, D3.1, D4.1, J1.1, J3.1, J4.1, J5.2, J6.13, J6.14, J6.20, J6.21, J6.22, J8.1, J9.6, Q1.2, R5.1, R6.1, R7.2, R9.1, S1.2, TH1.2, U1.2, U2.3, U2.5, U2.21, U3.2, U4.9, U5.1, Y1.2
unnamed: D4.2, R4.2
unnamed: D5.1, R5.2
unnamed: D6.1, R6.2
unnamed: F1.2, U1.3
unnamed: J2.1, R1.2
unnamed: L1.1, U3.7
unnamed: L1.3, U3.6
unnamed: Q1.3, R1.1
unnamed: R7.1, U3.8
unnamed: R8.2, U4.17
unnamed: R9.2, U5.23
unnamed: U3.1, U4.1
unnamed: U3.4, U4.2
unnamed: U4.7, Y1.3
unnamed: U4.8, Y1.1
RTD_BTN_LED: J1.3, U5.20
~FAULT_IND_1: J5.5, U5.5
~FAULT_IND_2: J5.4, U5.6
~FAULT_IND_3: J5.1, U5.7

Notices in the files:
parts and their libraries:
Copyright 2016 Accelerated Designs. All rights reserved.
